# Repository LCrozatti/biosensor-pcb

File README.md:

# biosensor-pcb

Development of a printed circuit with NFC communication that performs cyclic voltammetry and chronoamperometry on printed electrodes with applications in amperometric biosensors.

## :books: Methodology

Kicad software will be used to make the printed circuit boards, and the first PCB has the purpose to test the code and noise involved in the sampling. The test board in question has its files in the `./placa-teste` directory. The designed test board is illustrated in the figure below:

The first firmware involved was made based on code produced by [Linnes Lab](https://github.com/LinnesLab/LMP91000). Initially, an ATmega168PA-MU microcontroller will be used to control the potentiostat.

### :hammer: Tools

<br />

### :test_tube: Data analysis

The data will be analyzed using the Python language, the file `./placa-teste/amostragem/eletroquimica.ipynb` contains some demonstrations on the use of python in cyclic voltammetry and chronoamperometry operations. The dataset used in this file can be accessed through the [IEEE Data Port](https://ieee-dataport.org/documents/supplementary-material-optimized-sampling-rate-voltammetry-based-electrochemical-sensing) [1].

### :dart: Final prototype

The final board will have an antenna controlled by the *transponder* ST25DV64K, the control will be carried out by the microcontroller STM32L0 and the voltage control at the electrodes will be given through the programmable potentiostat LMP91000. The main study in this phase is the possibility of *energy harvesting*, leading to a circuit with low energy consumption.

### :iphone: App

The application in question will be built using the React-Native *framework*, along with the [react-native-nfc-manager](https://github.com/whitedogg13/react-native-nfc-manager) library. Its beginning has already been given with some reading tests..

## :hourglass: Timeline

### 06/06/2021

The repository was created and updated with data from the test board.

### 13/09/2021

The soldering of the components has been completed and now some tests are being done to confirm the code. There were some problems in the negative polarization part and I will now work on the IntZ variable to make this possible (67% Vref - when we work with negative polarization). So the positive bias is working and it is possible to do a "half" cyclic voltammetry.

### 12/10/2021

Another test was made and is possible to see that the potential between WE and RE is sweeping among -490 mV and 490 mV, demonstrating that the board is well functioning (24% of the reference voltage that is 2.048 V = 491,52 mV). Showing that the circuit can perform cyclic voltammetry in Potassium Ferrocyanide.

### 26/01/2022

The first PCB with NFC communication was developed, is being tested and the code of STM32L031G6U6 will be published here. To project the antenna, i used as a reference the Application note - AN2972 from ST Instruments and with some calculations the theoretic inductance obtained was 2.79 µH. Measuring with the help of a Handheld LCR Meter - UT612, the experimental inductance was 2.6 µH being an percent error of 7.3%.

## References

[1] S. Aiassa, S. Carrara and D. Demarchi, "Optimized Sampling Rate for Voltammetry-Based Electrochemical Sensing in Wearable and IoT Applications," in IEEE Sensors Letters. doi: 10.1109/LSENS.2019.2918575.

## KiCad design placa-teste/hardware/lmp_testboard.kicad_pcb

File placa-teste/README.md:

# placa-teste

Arquivos da primeira placa projetada.

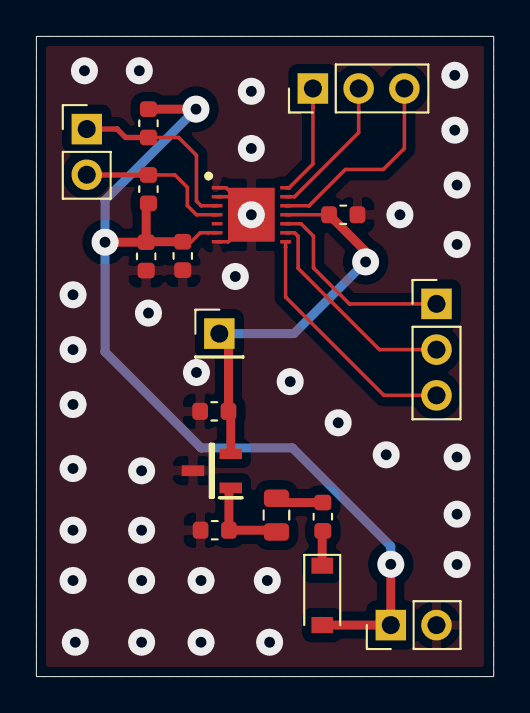
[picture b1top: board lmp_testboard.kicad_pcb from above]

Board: 2 copper layers, 25.4 x 35.6 mm, 17 parts (0 on the bottom side), 14 nets.

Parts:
C1: 0.47 uF; C_0603_1608Metric
C2, C5: 0.1uF; C_0603_1608Metric
C3: 1uF; C_0603_1608Metric
C4: 2.2 uF; C_0603_1608Metric
D1: B5819W; D_SOD-123
F1: 500mA; Fuse_0603_1608Metric
FB1: 100 @ 100 MHz; L_0805_2012Metric
IC1: LMP91000SD_NOPB; LMP91000SDX_NOPB
J1, J2: Conn_01x02; PinHeader_1x02_P2.54mm_Vertical
J3, J4: Conn_01x03; PinHeader_1x03_P2.54mm_Vertical
J5: Conn_01x01; PinHeader_1x01_P2.54mm_Vertical
R2, R3: 2k2; R_0603_1608Metric
U1: REF3020; SOT95P237X112-3N

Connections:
A0: IC1.8, J4.3
C1: IC1.10, J4.1
C2: IC1.9, J4.2
CE: IC1.14, J3.1
GND: C1.2, C2.2, C3.2, C4.2, C5.2, IC1.1, IC1.2, IC1.7, IC1.15, J1.2, U1.3
unnamed: C1.1, FB1.1, U1.1
unnamed: D1.1, F1.1
unnamed: F1.2, FB1.2
RE: IC1.13, J3.2
SCL: IC1.3, J2.1, R2.2
SDA: IC1.4, J2.2, R3.2
VCC: C4.1, C5.1, D1.2, IC1.6, J1.1, R2.1, R3.1
VREF: C2.1, C3.1, IC1.11, J5.1, U1.2
WE: IC1.12, J3.3

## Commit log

2020-10-02 Arquivos do circuito
2022-08-02 Adicionar mais comentários e possíveis edições
